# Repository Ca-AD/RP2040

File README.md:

# RP2040
PM2.5 程序是基于 Arduino 的，可做参考。

原理图

PCB

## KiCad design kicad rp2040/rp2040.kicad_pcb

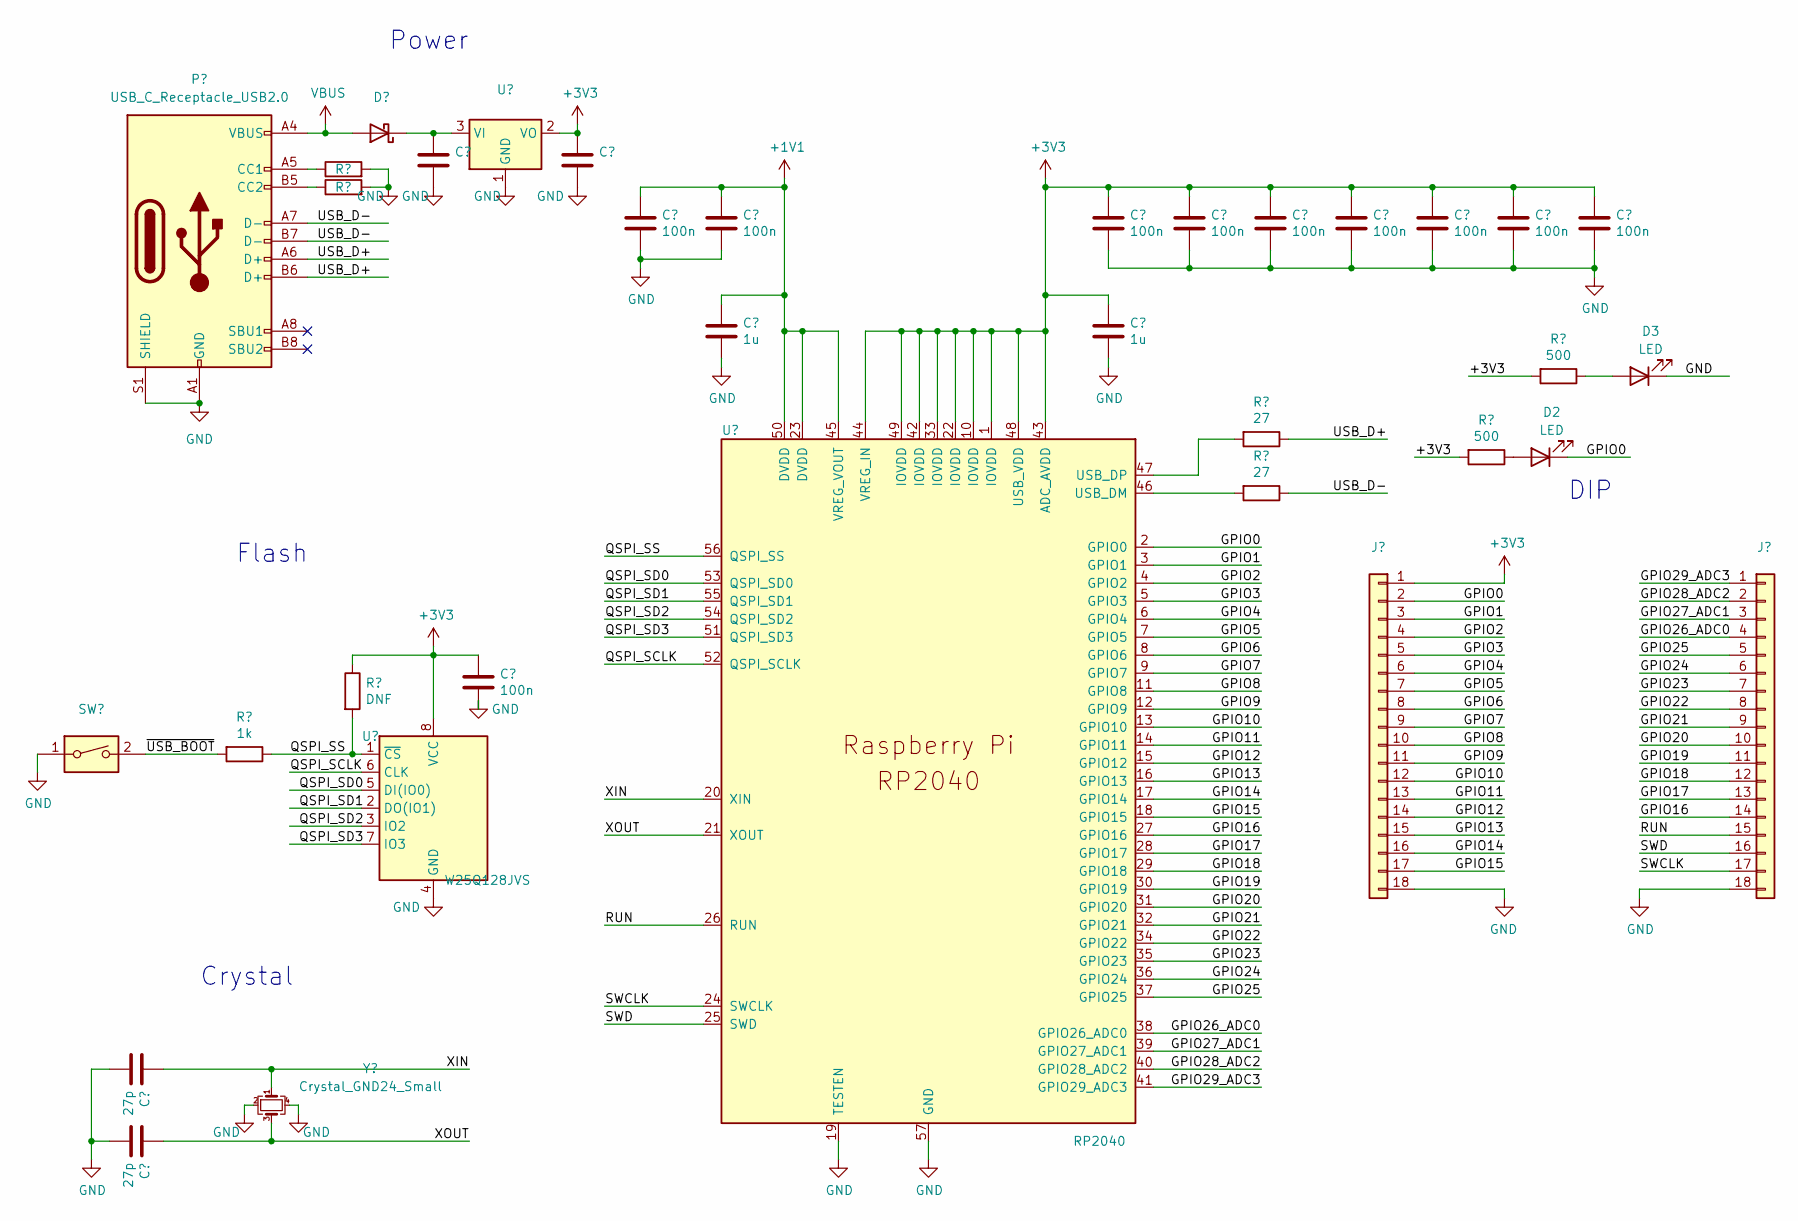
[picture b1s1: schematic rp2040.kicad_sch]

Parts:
C1, C2: 27p; C_0402_1005Metric
C3, C5: 10u; C_0805_2012Metric
C4, C6, C7, C9, C11, C12, C13, C14, C15, C16: 100n; C_0402_1005Metric
C8, C10: 1u; C_0402_1005Metric
D1: D_Schottky; SOD-323_L1.8-W1.3-LS2.5-RD
D2, D3: LED; LED_0402_1005Metric
J1, J2: Conn_01x18_MountingPin; PinHeader_1x18_P2.54mm_Vertical
P1: USB_C_Receptacle_USB2.0; USB_C_Receptacle_HRO_TYPE-C-31-M-12
R1: 1k; C_0402_1005Metric
R2, R3: 5.1k; C_0402_1005Metric
R4: DNF; C_0402_1005Metric
R5, R6: 27; C_0402_1005Metric
R7, R8: 500; C_0402_1005Metric
SW1: SW_DIP_x01; SW-SMD_L4.0-W3.0-LS5.0
U1: W25Q128JVS; SOIC-8_5.23x5.23mm_P1.27mm
U2: NCP1117-3.3_SOT223; SOT-223-3_TabPin2
U3: RP2040; RP2040-QFN-56
Y1: Crystal_GND24_Small; OSC-SMD_4P-L3.2-W2.5-BL

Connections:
+1V1: C6.1, C7.1, C8.1, U3.23 (DVDD), U3.45 (VREG_VOUT), U3.50 (DVDD)
+3V3: C4.1, C5.1, C9.1, C10.1, C11.1, C12.1, C13.1, C14.1, C15.1, C16.1, J1.1, R4.1, R7.2, R8.2, U1.8 (VCC), U2.2 (VO), U3.1 (IOVDD), U3.10 (IOVDD), U3.22 (IOVDD), U3.33 (IOVDD), U3.42 (IOVDD), U3.43 (ADC_AVDD), U3.44 (VREG_IN), U3.48 (USB_VDD), U3.49 (IOVDD)
/GPIO0: D2.1 (K), J1.2, U3.2 (GPIO0)
/GPIO1: J1.3, U3.3 (GPIO1)
/GPIO2: J1.4, U3.4 (GPIO2)
/GPIO3: J1.5, U3.5 (GPIO3)
/GPIO4: J1.6, U3.6 (GPIO4)
/GPIO5: J1.7, U3.7 (GPIO5)
/GPIO6: J1.8, U3.8 (GPIO6)
/GPIO7: J1.9, U3.9 (GPIO7)
/GPIO8: J1.10, U3.11 (GPIO8)
/GPIO9: J1.11, U3.12 (GPIO9)
/GPIO10: J1.12, U3.13 (GPIO10)
/GPIO11: J1.13, U3.14 (GPIO11)
/GPIO12: J1.14, U3.15 (GPIO12)
/GPIO13: J1.15, U3.16 (GPIO13)
/GPIO14: J1.16, U3.17 (GPIO14)
/GPIO15: J1.17, U3.18 (GPIO15)
/GPIO16: J2.14, U3.27 (GPIO16)
/GPIO17: J2.13, U3.28 (GPIO17)
/GPIO18: J2.12, U3.29 (GPIO18)
/GPIO19: J2.11, U3.30 (GPIO19)
/GPIO20: J2.10, U3.31 (GPIO20)
/GPIO21: J2.9, U3.32 (GPIO21)
/GPIO22: J2.8, U3.34 (GPIO22)
/GPIO23: J2.7, U3.35 (GPIO23)
/GPIO24: J2.6, U3.36 (GPIO24)
/GPIO25: J2.5, U3.37 (GPIO25)
/GPIO26_ADC0: J2.4, U3.38 (GPIO26_ADC0)
/GPIO27_ADC1: J2.3, U3.39 (GPIO27_ADC1)
/GPIO28_ADC2: J2.2, U3.40 (GPIO28_ADC2)
/GPIO29_ADC3: J2.1, U3.41 (GPIO29_ADC3)
/QSPI_SCLK: U1.6 (CLK), U3.52 (QSPI_SCLK)
/QSPI_SD0: U1.5 (DI(IO0)), U3.53 (QSPI_SD0)
/QSPI_SD1: U1.2 (DO(IO1)), U3.55 (QSPI_SD1)
/QSPI_SD2: U1.3 (IO2), U3.54 (QSPI_SD2)
/QSPI_SD3: U1.7 (IO3), U3.51 (QSPI_SD3)
/QSPI_SS: R1.1, R4.2, U1.1 (~CS), U3.56 (QSPI_SS); also elsewhere on the board
/RUN: J2.15, U3.26 (RUN)
/SWCLK: J2.17, U3.24 (SWCLK)
/SWD: J2.16, U3.25 (SWD)
/USB_D+: P1.A6 (D+), P1.B6 (D+), R5.1
/USB_D-: P1.A7 (D-), P1.B7 (D-), R6.1
/XIN: C1.1, U3.20 (XIN), Y1.1
/XOUT: C2.1, U3.21 (XOUT), Y1.3
/~USB_BOOT: R1.2, SW1.2; also elsewhere on the board
GND: C1.2, C2.2, C3.2, C4.2, C5.2, C6.2, C7.2, C8.2, C9.2, C10.2, C11.2, C12.2, C13.2, C14.2, C15.2, C16.2, D3.1 (K), J1.18, J2.18, P1.A1 (GND), P1.A12 (GND), P1.B1 (GND), P1.B12 (GND), P1.S1 (SHIELD), R2.2, R3.2, SW1.1, U1.4 (GND), U2.1 (GND), U3.19 (TESTEN), U3.57 (GND), Y1.2, Y1.4
unnamed: C3.1, D1.1 (K), U2.3 (VI)
unnamed: D2.2 (A), R8.1
unnamed: D3.2 (A), R7.1
unnamed: P1.A5 (CC1), R2.1
unnamed: P1.B5 (CC2), R3.1
unnamed: R6.2, U3.46 (USB_DM)
unnamed: R5.2, U3.47 (USB_DP)
VBUS: D1.2 (A), P1.A4 (VBUS), P1.A9 (VBUS), P1.B4 (VBUS), P1.B9 (VBUS)

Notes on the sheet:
Flash
Power
Crystal
DIP

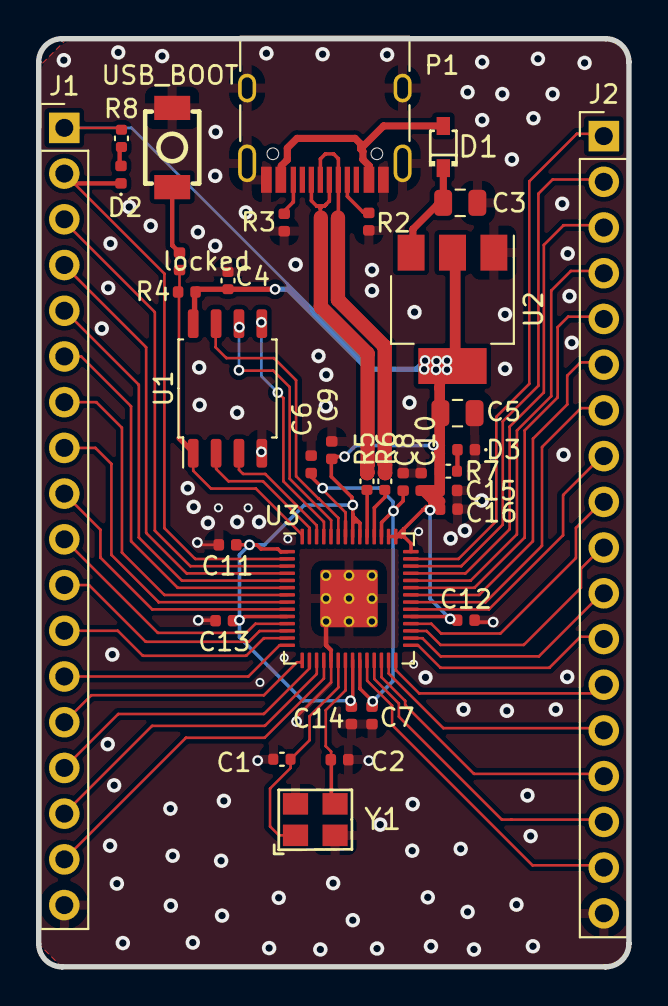
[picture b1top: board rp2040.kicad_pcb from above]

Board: 2 copper layers, 32.8 x 51.6 mm, 35 parts (0 on the bottom side), 55 nets.

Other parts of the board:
locked: 1k; C_0402_1005Metric

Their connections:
/QSPI_SS: locked.1; also elsewhere on the board
/~USB_BOOT: locked.2; also elsewhere on the board

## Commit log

2023-06-24 ld
    Arduino-PM2.5
2023-06-24 ld
    添加离线安装包
2025-03-13 添加图片
